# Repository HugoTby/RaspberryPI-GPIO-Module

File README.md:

# Introduction au GPIO

Les ports GPIO (General Purpose Input/Output) de Raspberry Pi sont des broches d'entrée/sortie configurables qui permettent à l'utilisateur de communiquer avec le monde extérieur en utilisant des signaux électriques. Voici une brève description des ports GPIO de Raspberry Pi :

    Les Raspberry Pi les plus courants (Modèle B) disposent de 40 broches GPIO.
    Les broches sont numérotées de 1 à 40, en partant du coin supérieur gauche et en se déplaçant vers la droite.
    Les broches 1, 2, 4, 6, 9, 14, 17, 20, 25, 30, 34 et 39 sont des broches de masse.
    Les broches 3 et 5 sont des broches de 3,3 V.
    Les broches 4 et 6 sont des broches de 5 V.
    Les broches 8, 10, 12, 16, 18, 22, 24, 26, 28, 32, 36 et 38 sont des broches GPIO.
    Les broches GPIO peuvent être configurées en entrée ou en sortie en fonction des besoins du projet.
    Les broches GPIO sont compatibles avec les niveaux de tension TTL (0 V - 3,3 V) et CMOS (0 V - 5 V).
    Les broches GPIO peuvent être utilisées pour contrôler des LED, des moteurs, des capteurs et d'autres périphériques électroniques.
    Les broches GPIO peuvent être programmées en utilisant différents langages de programmation, tels que Python, C et Scratch.

# Utilisation

Les broches GPIO peuvent être utilisées pour contrôler différents périphériques électroniques, tels que des LED, des moteurs et des capteurs. La programmation des broches GPIO peut être réalisée à l'aide de différents langages de programmation, tels que Python, C et Scratch.

# Configuration

Les broches GPIO peuvent être configurées en entrée ou en sortie en fonction des besoins du projet. La configuration des broches GPIO peut être réalisée à l'aide de différents outils logiciels, tels que Raspbian et WiringPi.

# Compatibilité

Les broches GPIO sont compatibles avec les niveaux de tension TTL (0 V - 3,3 V) et CMOS (0 V - 5 V), ce qui les rend compatibles avec une grande variété de périphériques électroniques. Cependant, il est important de prendre en compte les niveaux de tension lors de la conception d'un circuit utilisant des broches GPIO.
Références

Pour en savoir plus sur l'utilisation des broches GPIO de Raspberry Pi, vous pouvez consulter la documentation officielle de Raspberry Pi : https://www.raspberrypi.org/documentation/usage/gpio/

## Screenshots

## Author

- [Hugo T](https://www.github.com/HugoTby)

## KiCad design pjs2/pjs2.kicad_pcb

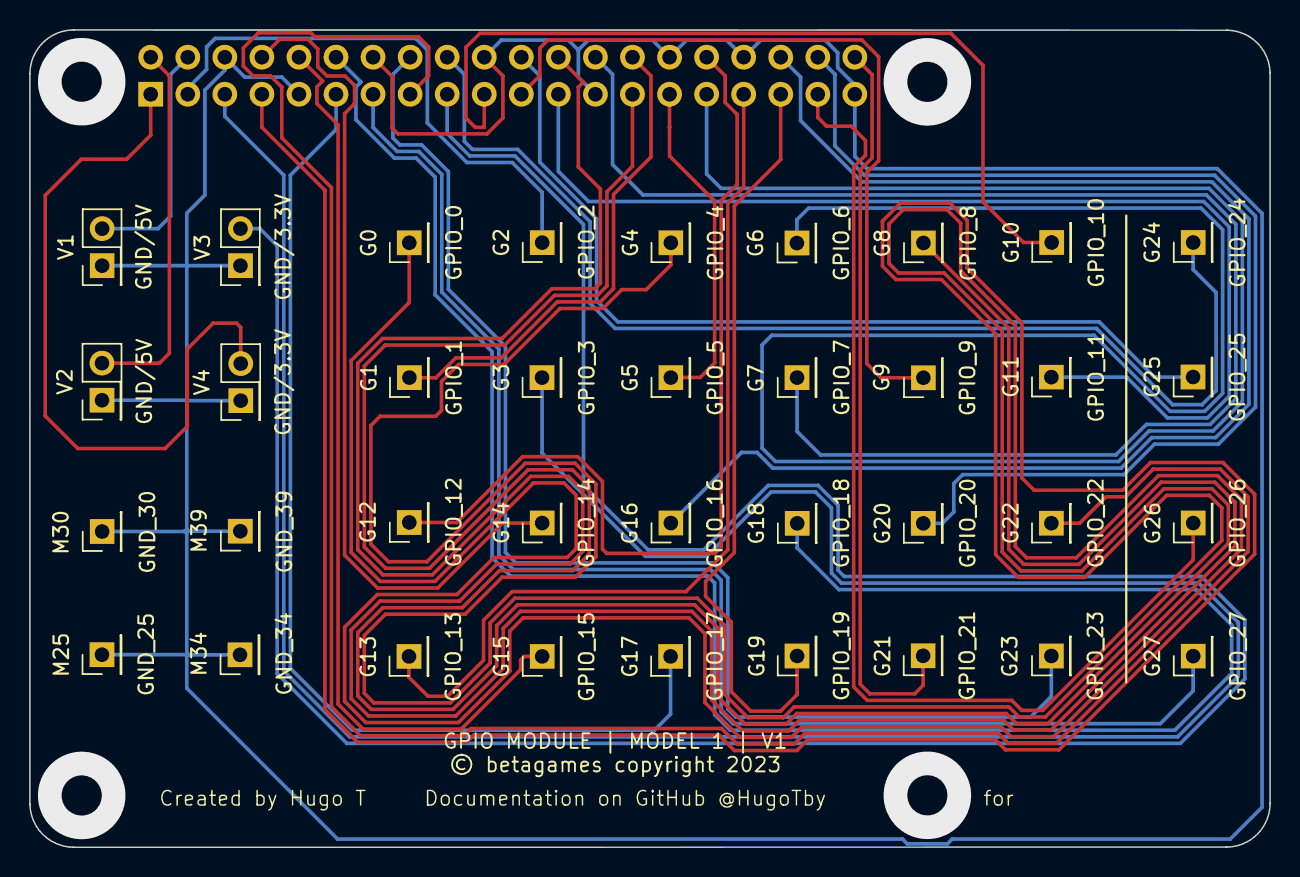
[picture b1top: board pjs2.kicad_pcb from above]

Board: 2 copper layers, 85.0 x 56.0 mm, 37 parts (1 on the bottom side), 33 nets.

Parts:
G0: GPIO_0; PinHeader_1x01_P2.54mm_Vertical
G1: GPIO_1; PinHeader_1x01_P2.54mm_Vertical
G2: GPIO_2; PinHeader_1x01_P2.54mm_Vertical
G3: GPIO_3; PinHeader_1x01_P2.54mm_Vertical
G4: GPIO_4; PinHeader_1x01_P2.54mm_Vertical
G5: GPIO_5; PinHeader_1x01_P2.54mm_Vertical
G6: GPIO_6; PinHeader_1x01_P2.54mm_Vertical
G7: GPIO_7; PinHeader_1x01_P2.54mm_Vertical
G8: GPIO_8; PinHeader_1x01_P2.54mm_Vertical
G9: GPIO_9; PinHeader_1x01_P2.54mm_Vertical
G10: GPIO_10; PinHeader_1x01_P2.54mm_Vertical
G11: GPIO_11; PinHeader_1x01_P2.54mm_Vertical
G12: GPIO_12; PinHeader_1x01_P2.54mm_Vertical
G13: GPIO_13; PinHeader_1x01_P2.54mm_Vertical
G14: GPIO_14; PinHeader_1x01_P2.54mm_Vertical
G15: GPIO_15; PinHeader_1x01_P2.54mm_Vertical
G16: GPIO_16; PinHeader_1x01_P2.54mm_Vertical
G17: GPIO_17; PinHeader_1x01_P2.54mm_Vertical
G18: GPIO_18; PinHeader_1x01_P2.54mm_Vertical
G19: GPIO_19; PinHeader_1x01_P2.54mm_Vertical
G20: GPIO_20; PinHeader_1x01_P2.54mm_Vertical
G21: GPIO_21; PinHeader_1x01_P2.54mm_Vertical
G22: GPIO_22; PinHeader_1x01_P2.54mm_Vertical
G23: GPIO_23; PinHeader_1x01_P2.54mm_Vertical
G24: GPIO_24; PinHeader_1x01_P2.54mm_Vertical
G25: GPIO_25; PinHeader_1x01_P2.54mm_Vertical
G26: GPIO_26; PinHeader_1x01_P2.54mm_Vertical
G27: GPIO_27; PinHeader_1x01_P2.54mm_Vertical
J3: Raspberry_Pi_2_3; PinSocket_2x20_P2.54mm_Vertical
M25: GND_25; PinHeader_1x01_P2.54mm_Vertical
M30: GND_30; PinHeader_1x01_P2.54mm_Vertical
M34: GND_34; PinHeader_1x01_P2.54mm_Vertical
M39: GND_39; PinHeader_1x01_P2.54mm_Vertical
V1, V2: GND/5V; PinHeader_2x01_P2.54mm_Vertical
V3, V4: GND/3.3V; PinHeader_2x01_P2.54mm_Vertical

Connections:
unnamed: J3.6 (GND), J3.9 (GND), J3.14 (GND), J3.20 (GND), J3.25 (GND), J3.30 (GND), J3.34 (GND), J3.39 (GND), M25.1, M30.1, M34.1, M39.1, V1.1, V2.1, V3.1, V4.1
unnamed: J3.4 (5V), V1.2
unnamed: J3.2 (5V), V2.2
unnamed: J3.17 (3V3), V3.2
unnamed: J3.1 (3V3), V4.2
unnamed: G0.1, J3.27 (ID_SD/GPIO0)
unnamed: G1.1, J3.28 (ID_SC/GPIO1)
unnamed: G2.1, J3.3 (SDA/GPIO2)
unnamed: G3.1, J3.5 (SCL/GPIO3)
unnamed: G4.1, J3.7 (GCLK0/GPIO4)
unnamed: G5.1, J3.29 (GCLK1/GPIO5)
unnamed: G6.1, J3.31 (GCLK2/GPIO6)
unnamed: G7.1, J3.26 (~CE1/GPIO7)
unnamed: G8.1, J3.24 (~CE0/GPIO8)
unnamed: G9.1, J3.21 (MISO0/GPIO9)
unnamed: G10.1, J3.19 (MOSI0/GPIO10)
unnamed: G11.1, J3.23 (SCLK0/GPIO11)
unnamed: G12.1, J3.32 (PWM0/GPIO12)
unnamed: G13.1, J3.33 (PWM1/GPIO13)
unnamed: G14.1, J3.8 (GPIO14/TXD)
unnamed: G15.1, J3.10 (GPIO15/RXD)
unnamed: G16.1, J3.36 (GPIO16)
unnamed: G17.1, J3.11 (GPIO17)
unnamed: G18.1, J3.12 (GPIO18/PWM0)
unnamed: G19.1, J3.35 (GPIO19/MISO1)
unnamed: G20.1, J3.38 (GPIO20/MOSI1)
unnamed: G21.1, J3.40 (GPIO21/SCLK1)
unnamed: G22.1, J3.15 (GPIO22)
unnamed: G23.1, J3.16 (GPIO23)
unnamed: G24.1, J3.18 (GPIO24)
unnamed: G25.1, J3.22 (GPIO25)
unnamed: G26.1, J3.37 (GPIO26)
unnamed: G27.1, J3.13 (GPIO27)

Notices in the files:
pjs2/pjs2.kicad_pcb:
HugoTby © copyright 2023
© betagames copyright 2023
